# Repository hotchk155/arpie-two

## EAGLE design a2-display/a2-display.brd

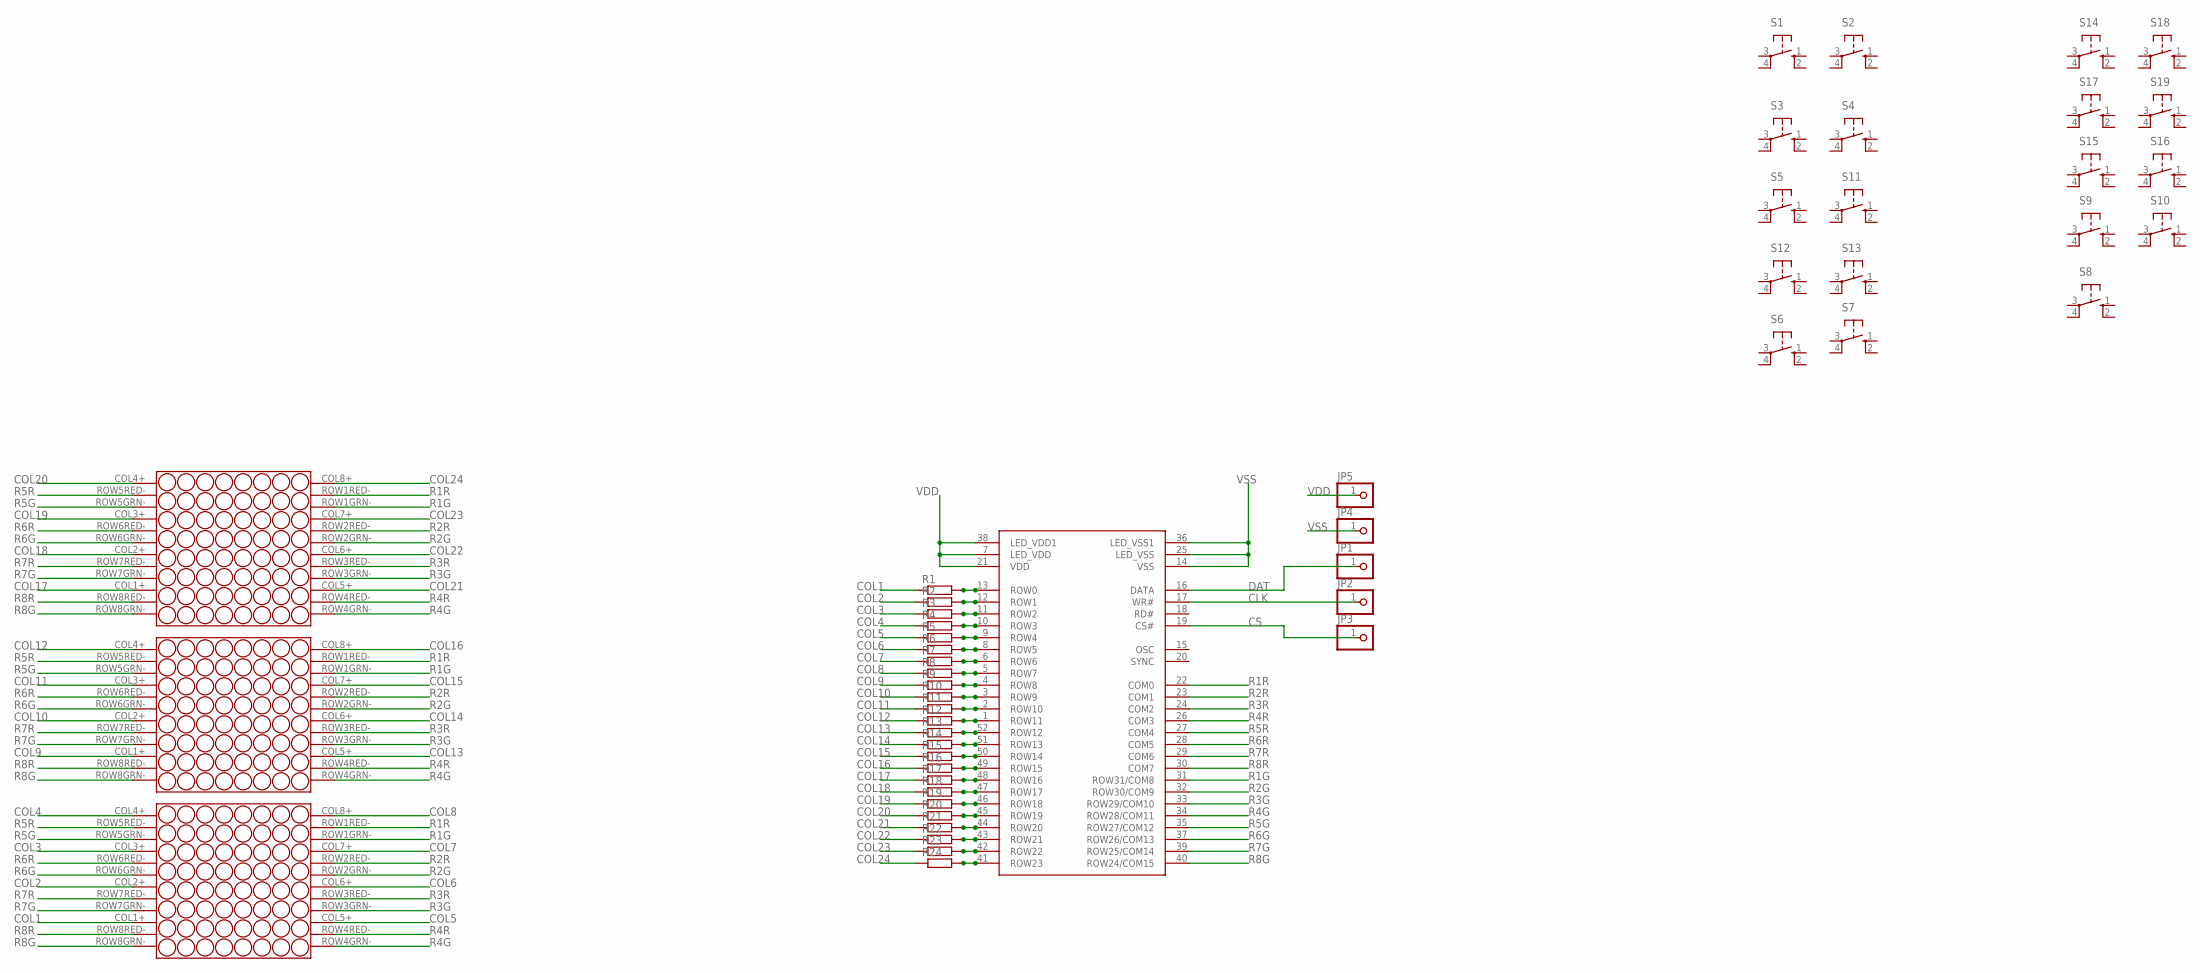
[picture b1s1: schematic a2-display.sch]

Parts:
IC1: HT1632C; QFP52
JP1, JP2, JP3, JP4, JP5: PINHD-1X1; 1X01
R1, R2, R3, R4, R5, R6, R7, R8, R9, R10, R11, R12, R13, R14, R15, R16, R17, R18, R19, R20, R21, R22, R23, R24: R-EU_R0805; R0805
S1, S2, S3, S4, S5, S6, S7, S8, S9, S10, S11, S12, S13, S14, S15, S16, S17, S18, S19: 10-XX; B3F-10XX
U$1, U$2, U$3: 8X8; SURE8X8

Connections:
CLK: IC1.17 (WR#), JP2.1
COL1: R1.1, U$3.COL1+ (COL1_AN)
COL2: R2.1, U$3.COL2+ (COL2_AN)
COL3: R3.1, U$3.COL3+ (COL3_AN)
COL4: R4.1, U$3.COL4+ (COL4_AN)
COL5: R5.1, U$3.COL5+ (COL5_AN)
COL6: R6.1, U$3.COL6+ (COL6_AN)
COL7: R7.1, U$3.COL7+ (COL7_AN)
COL8: R8.1, U$3.COL8+ (COL8_AN)
COL9: R9.1, U$2.COL1+ (COL1_AN)
COL10: R10.1, U$2.COL2+ (COL2_AN)
COL11: R11.1, U$2.COL3+ (COL3_AN)
COL12: R12.1, U$2.COL4+ (COL4_AN)
COL13: R13.1, U$2.COL5+ (COL5_AN)
COL14: R14.1, U$2.COL6+ (COL6_AN)
COL15: R15.1, U$2.COL7+ (COL7_AN)
COL16: R16.1, U$2.COL8+ (COL8_AN)
COL17: R17.1, U$1.COL1+ (COL1_AN)
COL18: R18.1, U$1.COL2+ (COL2_AN)
COL19: R19.1, U$1.COL3+ (COL3_AN)
COL20: R20.1, U$1.COL4+ (COL4_AN)
COL21: R21.1, U$1.COL5+ (COL5_AN)
COL22: R22.1, U$1.COL6+ (COL6_AN)
COL23: R23.1, U$1.COL7+ (COL7_AN)
COL24: R24.1, U$1.COL8+ (COL8_AN)
CS: IC1.19 (CS#), JP3.1
DAT: IC1.16 (DATA), JP1.1
unnamed: IC1.13 (ROW0), R1.2
unnamed: IC1.12 (ROW1), R2.2
unnamed: IC1.11 (ROW2), R3.2
unnamed: IC1.10 (ROW3), R4.2
unnamed: IC1.9 (ROW4), R5.2
unnamed: IC1.8 (ROW5), R6.2
unnamed: IC1.6 (ROW6), R7.2
unnamed: IC1.5 (ROW7), R8.2
unnamed: IC1.4 (ROW8), R9.2
unnamed: IC1.3 (ROW9), R10.2
unnamed: IC1.2 (ROW10), R11.2
unnamed: IC1.1 (ROW11), R12.2
unnamed: IC1.52 (ROW12), R13.2
unnamed: IC1.51 (ROW13), R14.2
unnamed: IC1.50 (ROW14), R15.2
unnamed: IC1.49 (ROW15), R16.2
unnamed: IC1.48 (ROW16), R17.2
unnamed: IC1.47 (ROW17), R18.2
unnamed: IC1.46 (ROW18), R19.2
unnamed: IC1.45 (ROW19), R20.2
unnamed: IC1.44 (ROW20), R21.2
unnamed: IC1.43 (ROW21), R22.2
unnamed: IC1.42 (ROW22), R23.2
unnamed: IC1.41 (ROW23), R24.2
R1G: IC1.31 (ROW31/COM8), U$1.ROW1GRN- (GRN1_CA), U$2.ROW1GRN- (GRN1_CA), U$3.ROW1GRN- (GRN1_CA)
R1R: IC1.22 (COM0), U$1.ROW1RED- (RED1_CA), U$2.ROW1RED- (RED1_CA), U$3.ROW1RED- (RED1_CA)
R2G: IC1.32 (ROW30/COM9), U$1.ROW2GRN- (GRN2_CA), U$2.ROW2GRN- (GRN2_CA), U$3.ROW2GRN- (GRN2_CA)
R2R: IC1.23 (COM1), U$1.ROW2RED- (RED2_CA), U$2.ROW2RED- (RED2_CA), U$3.ROW2RED- (RED2_CA)
R3G: IC1.33 (ROW29/COM10), U$1.ROW3GRN- (GRN3_CA), U$2.ROW3GRN- (GRN3_CA), U$3.ROW3GRN- (GRN3_CA)
R3R: IC1.24 (COM2), U$1.ROW3RED- (RED3_CA), U$2.ROW3RED- (RED3_CA), U$3.ROW3RED- (RED3_CA)
R4G: IC1.34 (ROW28/COM11), U$1.ROW4GRN- (GRN4_CA), U$2.ROW4GRN- (GRN4_CA), U$3.ROW4GRN- (GRN4_CA)
R4R: IC1.26 (COM3), U$1.ROW4RED- (RED4_CA), U$2.ROW4RED- (RED4_CA), U$3.ROW4RED- (RED4_CA)
R5G: IC1.35 (ROW27/COM12), U$1.ROW5GRN- (GRN5_CA), U$2.ROW5GRN- (GRN5_CA), U$3.ROW5GRN- (GRN5_CA)
R5R: IC1.27 (COM4), U$1.ROW5RED- (RED5_CA), U$2.ROW5RED- (RED5_CA), U$3.ROW5RED- (RED5_CA)
R6G: IC1.37 (ROW26/COM13), U$1.ROW6GRN- (GRN6_CA), U$2.ROW6GRN- (GRN6_CA), U$3.ROW6GRN- (GRN6_CA)
R6R: IC1.28 (COM5), U$1.ROW6RED- (RED6_CA), U$2.ROW6RED- (RED6_CA), U$3.ROW6RED- (RED6_CA)
R7G: IC1.39 (ROW25/COM14), U$1.ROW7GRN- (GRN7_CA), U$2.ROW7GRN- (GRN7_CA), U$3.ROW7GRN- (GRN7_CA)
R7R: IC1.29 (COM6), U$1.ROW7RED- (RED7_CA), U$2.ROW7RED- (RED7_CA), U$3.ROW7RED- (RED7_CA)
R8G: IC1.40 (ROW24/COM15), U$1.ROW8GRN- (GRN8_CA), U$2.ROW8GRN- (GRN8_CA), U$3.ROW8GRN- (GRN8_CA)
R8R: IC1.30 (COM7), U$1.ROW8RED- (RED8_CA), U$2.ROW8RED- (RED8_CA), U$3.ROW8RED- (RED8_CA)
VDD: IC1.7 (LED_VDD), IC1.21 (VDD), IC1.38 (LED_VDD1), JP5.1
VSS: IC1.14 (VSS), IC1.25 (LED_VSS), IC1.36 (LED_VSS1), JP4.1

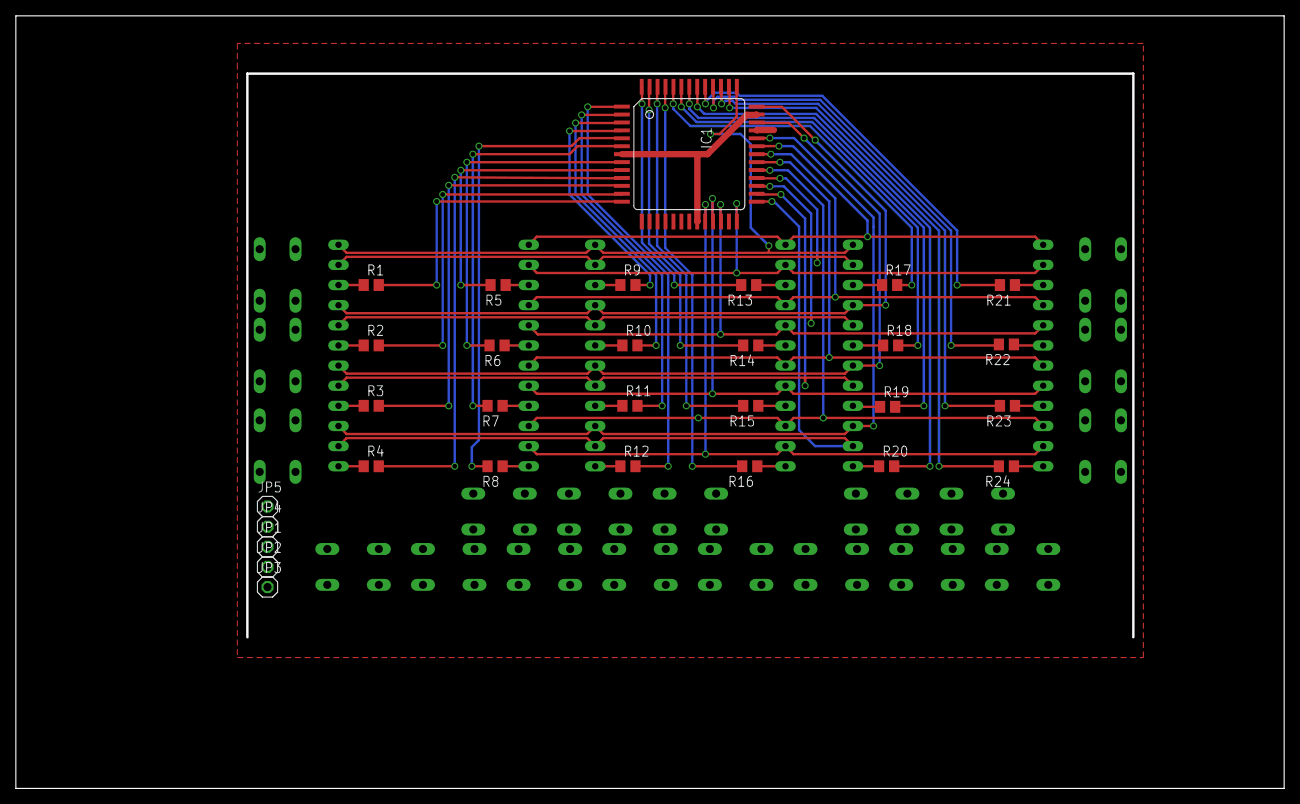
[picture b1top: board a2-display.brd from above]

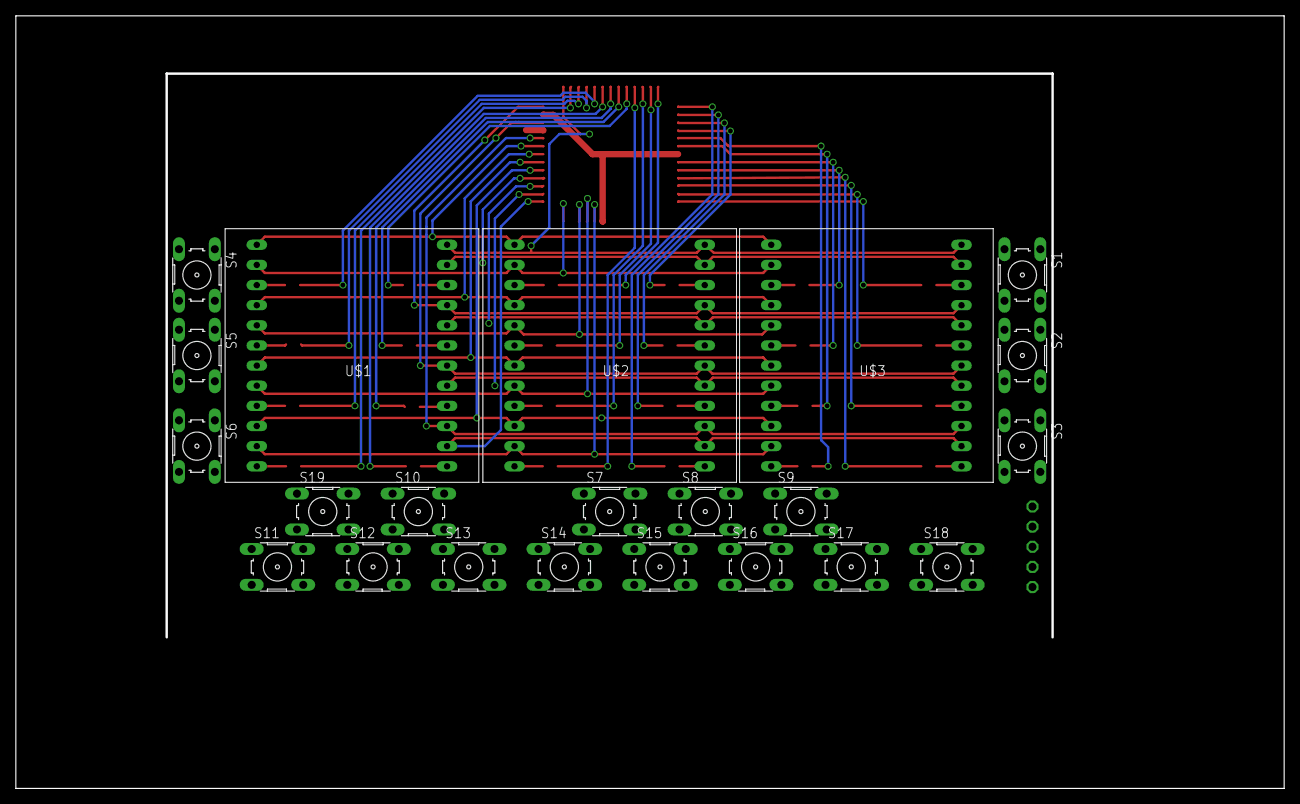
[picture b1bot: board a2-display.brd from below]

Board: 2 copper layers, 159.7 x 97.2 mm, 52 parts (22 on the bottom side), 69 nets.

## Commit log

2016-01-27 :octocat: Added .gitattributes & .gitignore files
2016-01-27 first
2016-01-28 stuff
